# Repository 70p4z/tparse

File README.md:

# TParse

A minimalistic C library to parse text in microcontroller without memory allocation.

Supports:
- Hex arrays
- Hex integer
- Decimal integer
- List of allowed keywords
- Raw text token fetch

## IOBridge
A basic iobridge example project is provided, making extended use of the library.
The project is splitted in:
- A iobridge application for NUCLEO-L476RG;
- A python (3) library to communicate with.

The iobridge goal is to offer an UART driven text interface to bridge to various protocols (raw GPIO, I2C bus, CAN bus, ISO7816-3 T=0). The project will be extended with ADC, OneWire and SPI.

## Nucleo F767ZI solax pylontech
Sometimes it's harder than it looks to build a solar system with batteries from scratch. Especially if you build it from the electronic engineer point of view.
Voltage are in range, and the datasheets seems like a match. 
BUT it turns out you're missing the whole point. Many players in the ecosystem are not willing for compatibility. And the war moves from electronic to communication protocol to make systems work.

I got into such a refreshing problem when I decided to go solar with a huge amount of auto consumption. I went for modular Pylontech H48050 (high voltage (HV)) based system (SC0500 + 8 H48050 in the end). And tried to connect it with a Solax X1 Hybrid G4.

The very point is that it won't work until you ~handle~ rewrite some part of the protocol on the fly.

The example for nucleo was mainly done to have the communication working, and various tries to allow for power optimisation, or workaround on problems (not respected zero injection).

Anyway, this project is only based on tparse for the ring buffer management (but it started with 2 iobridges until I found a board (f767zi) that handle 2 CAN bus to perform the man-in-the-middle).

The project further grown into a fully fledged reporting system to connect with home assistant (through a http sensor python script running on a raspberry pi zero w).

I'll try to add a design later on to design the daughter board on the nucleo for the various connections (mate box relay, CAN to the inverter, CAN to the battery, I2C for the reporting, serial for the pocket wifi link).

Long story short, the bugfix for the protocol is to only patch the CAN message 0x1877 byte 4 from whatever (IIRC it was 0x01) to 0x83 to make the inverter happily use the BMS (and stop complaining about invalid voltage).

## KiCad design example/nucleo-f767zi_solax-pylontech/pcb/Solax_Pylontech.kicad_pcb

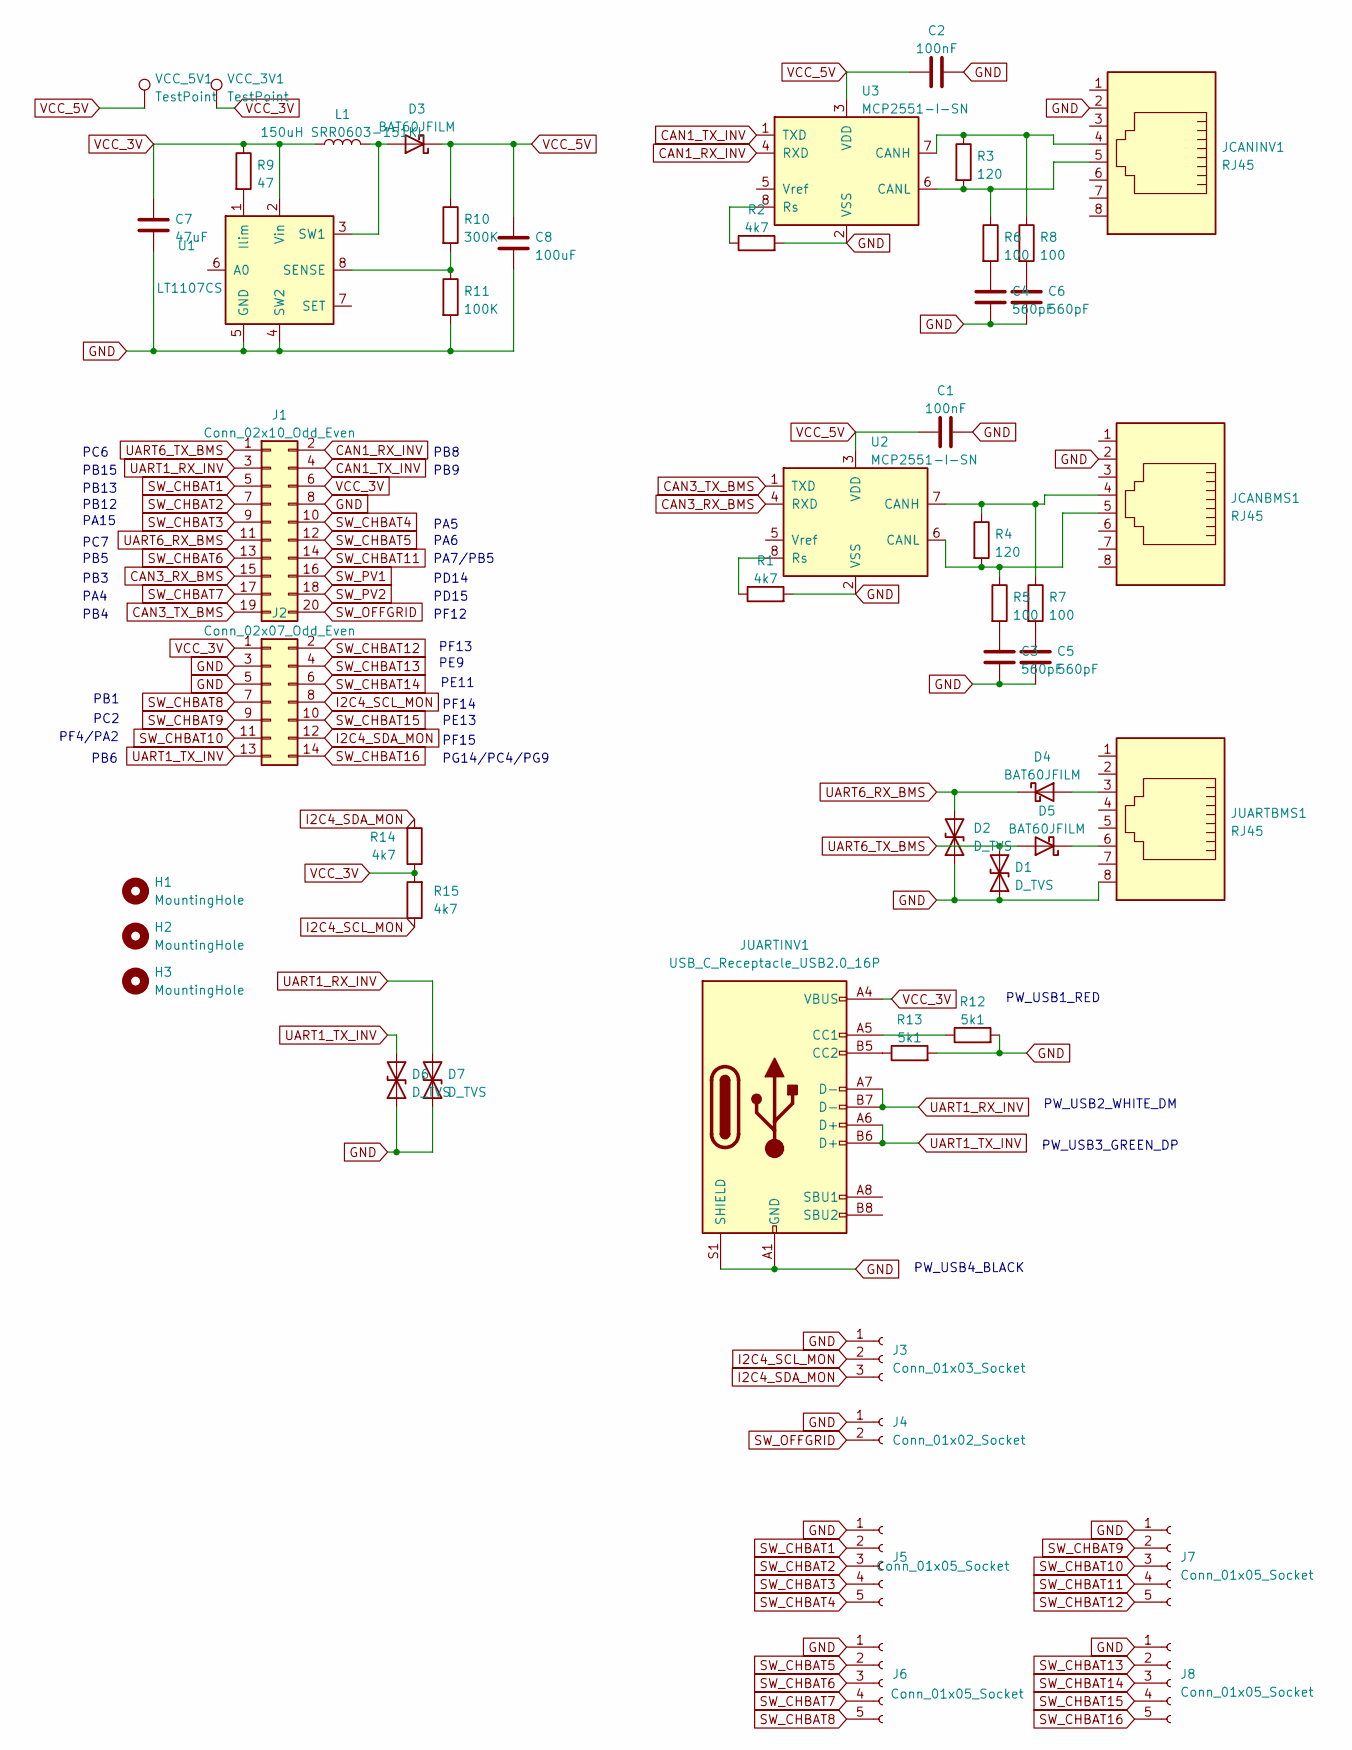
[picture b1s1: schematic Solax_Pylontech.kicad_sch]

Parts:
C1, C2: 100nF; C_0603_1608Metric
C3, C4, C5, C6: 560pF; C_0603_1608Metric
C7: 47uF; C_0805_2012Metric
C8: 100uF; C_0805_2012Metric
D1, D2, D6, D7: D_TVS; D_0603_1608Metric
D3, D4, D5: BAT60JFILM; D_SOD-323
H1, H2, H3: MountingHole; MountingHole_3mm
J1: Conn_02x10_Odd_Even; PinHeader_2x10_P2.54mm_Vertical
J2: Conn_02x07_Odd_Even; PinHeader_2x07_P2.54mm_Vertical
J3: Conn_01x03_Socket; JST_XH_B3B-XH-A_1x03_P2.50mm_Vertical
J4: Conn_01x02_Socket; JST_XH_B2B-XH-A_1x02_P2.50mm_Vertical
J5, J6, J7, J8: Conn_01x05_Socket; JST_XH_B5B-XH-A_1x05_P2.50mm_Vertical
JCANBMS1: RJ45; RJ45_Amphenol_54602-x08_Horizontal
JCANINV1: RJ45; RJ45_Amphenol_54602-x08_Horizontal
JUARTBMS1: RJ45; RJ45_Amphenol_54602-x08_Horizontal
JUARTINV1: USB_C_Receptacle_USB2.0_16P; USB_C_Receptacle_GCT_USB4105-xx-A_16P_TopMnt_Horizontal
L1: 150uH SRR0603-151KL; L_6.3x6.3_H3
R1, R2, R14, R15: 4k7; R_0603_1608Metric
R3, R4: 120; R_0603_1608Metric
R5, R6, R7, R8: 100; R_0603_1608Metric
R9: 47; R_0603_1608Metric
R10: 300K; R_0603_1608Metric
R11: 100K; R_0603_1608Metric
R12, R13: 5k1; R_0603_1608Metric
U1: LT1107CS; SOIC-8_3.9x4.9mm_P1.27mm
U2, U3: MCP2551-I-SN; SOIC-8_3.9x4.9mm_P1.27mm
VCC_3V1, VCC_5V1: TestPoint; TestPoint_THTPad_D2.0mm_Drill1.0mm

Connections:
CAN1_RX_INV: J1.2, U3.4 (RXD)
CAN1_TX_INV: J1.4, U3.1 (TXD)
CAN3_RX_BMS: J1.15, U2.4 (RXD)
CAN3_TX_BMS: J1.19, U2.1 (TXD)
GND: C1.2, C2.1, C3.2, C4.2, C5.2, C6.2, C7.2, C8.1, D1.1 (A1), D2.1 (A1), D6.1 (A1), D7.1 (A1), J1.8, J2.3, J2.5, J3.1, J4.1, J5.1, J6.1, J7.1, J8.1, JCANBMS1.2, JCANINV1.2, JUARTBMS1.8, JUARTINV1.A1 (GND), JUARTINV1.A12 (GND), JUARTINV1.B1 (GND), JUARTINV1.B12 (GND), JUARTINV1.S1 (SHIELD), R1.2, R2.2, R11.2, R12.2, R13.2, U1.4 (SW2), U1.5 (GND), U2.2 (VSS), U3.2 (VSS)
I2C4_SCL_MON: J2.8, J3.2, R15.1
I2C4_SDA_MON: J2.12, J3.3, R14.2
unnamed: C3.1, R5.2
unnamed: C4.1, R6.2
unnamed: C5.1, R7.2
unnamed: C6.1, R8.2
unnamed: D3.2 (A), L1.2, U1.3 (SW1)
unnamed: D4.2 (A), JUARTBMS1.3
unnamed: D5.1 (K), JUARTBMS1.6
unnamed: JUARTINV1.A5 (CC1), R12.1
unnamed: JUARTINV1.B5 (CC2), R13.1
unnamed: R9.2, U1.1 (Ilim)
unnamed: R10.2, R11.1, U1.8 (SENSE)
unnamed: JCANBMS1.4, R4.1, R7.1, U2.7 (CANH)
unnamed: JCANBMS1.5, R4.2, R5.1, U2.6 (CANL)
unnamed: R1.1, U2.8 (Rs)
unnamed: JCANINV1.4, R3.1, R8.1, U3.7 (CANH)
unnamed: JCANINV1.5, R3.2, R6.1, U3.6 (CANL)
unnamed: R2.1, U3.8 (Rs)
SW_CHBAT1: J1.5, J5.2
SW_CHBAT2: J1.7, J5.3
SW_CHBAT3: J1.9, J5.4
SW_CHBAT4: J1.10, J5.5
SW_CHBAT5: J1.12, J6.2
SW_CHBAT6: J1.13, J6.3
SW_CHBAT7: J1.17, J6.4
SW_CHBAT8: J2.7, J6.5
SW_CHBAT9: J2.9, J7.2
SW_CHBAT10: J2.11, J7.3
SW_CHBAT11: J1.14, J7.4
SW_CHBAT12: J2.2, J7.5
SW_CHBAT13: J2.4, J8.2
SW_CHBAT14: J2.6, J8.3
SW_CHBAT15: J2.10, J8.4
SW_CHBAT16: J2.14, J8.5
SW_OFFGRID: J1.20, J4.2
SW_PV1: J1.16
SW_PV2: J1.18
UART1_RX_INV: D7.2 (A2), J1.3, JUARTINV1.A7 (D-), JUARTINV1.B7 (D-)
UART1_TX_INV: D6.2 (A2), J2.13, JUARTINV1.A6 (D+), JUARTINV1.B6 (D+)
UART6_RX_BMS: D2.2 (A2), D4.1 (K), J1.11
UART6_TX_BMS: D1.2 (A2), D5.2 (A), J1.1
VCC_3V: C7.1, J1.6, J2.1, JUARTINV1.A4 (VBUS), JUARTINV1.A9 (VBUS), JUARTINV1.B4 (VBUS), JUARTINV1.B9 (VBUS), L1.1, R9.1, R14.1, R15.2, U1.2 (Vin), VCC_3V1.1
VCC_5V: C1.1, C2.2, C8.2, D3.1 (K), R10.1, U2.3 (VDD), U3.3 (VDD), VCC_5V1.1

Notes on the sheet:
PA4
PD14
PA6
PC6
PB13
PB3
PB15
PW_USB3_GREEN_DP
PE9
PA7/PB5
PD15
PC2
PB9
PB8
PB5
PB4
PW_USB2_WHITE_DM
PC7
PE11
PF14
PG14/PC4/PG9
PE13
PW_USB1_RED
PA15
PW_USB4_BLACK
PF13
PB12
PB1
PF4/PA2
PF15
PF12
PA5
PB6

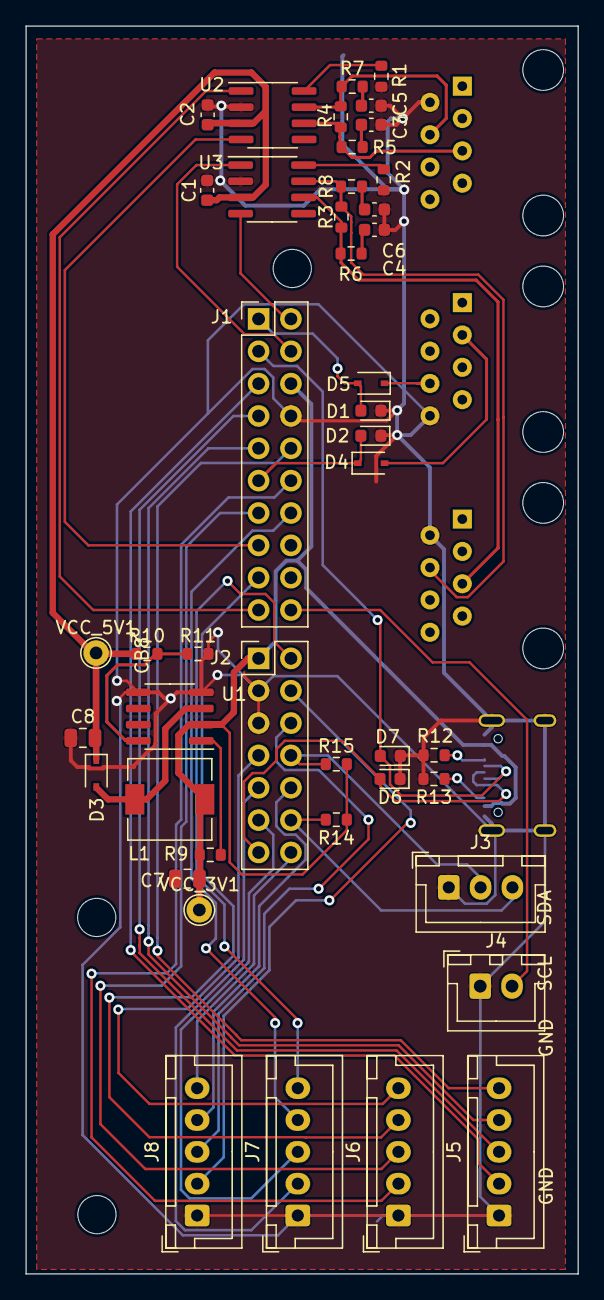
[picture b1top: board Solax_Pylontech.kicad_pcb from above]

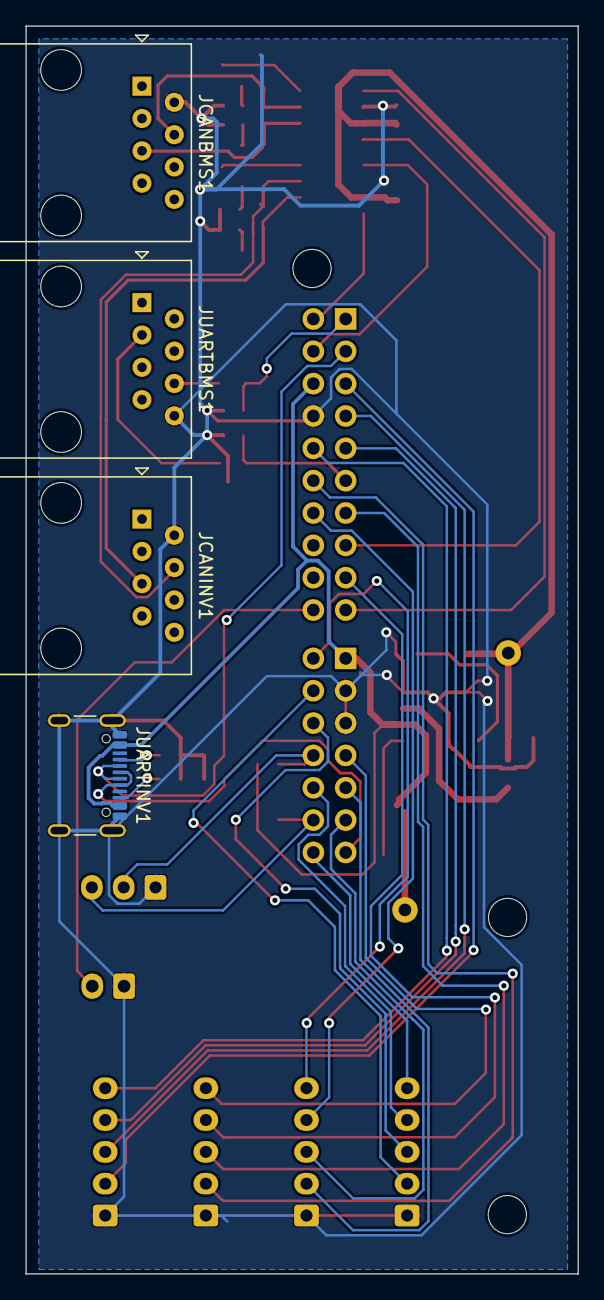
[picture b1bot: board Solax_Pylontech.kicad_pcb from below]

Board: 2 copper layers, 43.4 x 98.0 mm, 51 parts (4 on the bottom side), 47 nets.

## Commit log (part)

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2022-05-04 initial import
2022-05-05 stm32l476 iobridge
2022-05-07 add token_count for the unconsommed line + tests, add eol_reached check
2022-05-07 iobridge exti in polling (sometimes, it was not detected 8|), move timeout definition
2022-05-16 fix token_size to correctly return when token is at end of buffer, and delimiter is on the first buffer entry (i.e. "\n...token")
2022-05-17 remove debug stuff for previous token at end of buffer bug
2022-05-17 iobridge python for can bus with fixed mitm example
2022-05-22 fix out of bound receiving can frames
2022-05-22 fix i2c_cargo transport python script
2022-05-23 discard problematic tx requests
2022-05-30 - add i2c retry count to command in case of NAKed addresses - refactor iobridge uart sync
2022-06-07 - update usart<->pc bitrate - add isocfg and i2cfg commands - support ATR TA1 force to try negociating over the proposed max of a smartcard - fixup gpi command in case of unconfgured pin (must not be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
2022-06-08 update bitrate of the iobridge in its various base tools
2022-06-18 fixup swapped comments
2022-06-20 solax bms: add timeout during cavail requests, and add bms ping to startup the BMS without grid (to power up the off grid mode
2022-06-20 fix invalid i2c address check
2022-07-19 allow to set the i2c int pin with cargo operations
2022-08-30 fixup io troubles during transport of cached T0 APDU => python timeout in case of hard timeout
2022-10-16 store the first description of the BMS at boot
2022-10-31 change output files to avoid stm32cubeprogrammer to complain (not finding files)
2022-11-03 i2c: add clock (bitrate) configuration
2022-11-15 bump bridge's version and make use of i2c cached transfers to optimize the whole applications
2022-12-01 resynch slave board at startup for Pylontech/Solax correct communication
2022-12-16 add tparse_discard implementation
2022-12-17 fix chec to avoid disurbing battery SoC at night
2022-12-27 fix solax patch optimization for dawn/dusk and low solar
2022-12-27 solax: split invalidity checks to enhance user display
2022-12-27 solax bridge: commit output file for the solax master
2022-12-29 enhance battery display (try to correct the inverter battery invalid value)
2022-12-31 - more code annotation - reverse sign of export constan for easier computation understanding - add condition when engaging selfuse and not reached the 80% SoC, to ensure the battery continues to char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
2023-01-03 - reduce work mode change delay - fix invalid can standard marker - fix typo
2023-01-08 fixup CAN timings to avoid pylontech desynch
2023-01-08 only override max charge when not 100% SoC
2023-01-08 - fix battery wattage display (in both charge and discharge) - avoid wattage min value for self use switch rule when soc above threshold - set charge to 0A when overriding the mode (to forced stop)
2023-01-08 add cause display index for selfuse return rule
2023-01-10 put solax/pylontech var globals, and wipe them
2023-01-10 reencode errors, avoid dispaing with errors
2023-01-10 add i2c data output for home automation
2023-01-14 - add prints on the master uart for debug purpose - fixup rule 7 to avoid reporting battery charge max - fixup rule 5 requirement (grid_wattage must be over the optimization threshold (to debounce sm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
2023-01-16 force battery to 100% from the inverter point of view in optimization cases
2023-01-27 - refactor naming, output more data toward home assistant
2023-01-27 add a watchdog and a software io stall timeout to reset the bridge whenever a bad condition is detected
2023-03-21 try to fix a spurious overflow
2023-03-21 add fields (eps and pv state)
2023-03-23 fix definition of buffer size, also support pocketwifi regular settings read that kills the values (with a race condition on buffer access)
2023-04-04 add the previous version
2023-04-16 - add support for BMS RS232 precise current reading - rework pinout to minimize daughter board on nucleo - add daughter board design and gerbers for nucleo-f767zi - change type for 8 H48050 packs con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
2023-04-17 tparse: add test to parse negative integers example/nucleo/solax: add rendered schematic as pdf
2023-04-25 iobridge update to support mtu negociation and factorize all instructions for I2C cargo transport
2023-05-09 fix invlid inner loop exit during cargo i2c transfer
2023-05-14 fixup rs232 current direction on the pylontech SC0500-40s BMS
2023-06-06 silly previous patch reworked
2023-06-14 - bump version - add pylontech CAN cache to avoid power loss upon temporary CAN bus glitch - fix CAN bus 500kbit/s timing on STM32 bxCAN - add 98% SoC battery drain before PV powering bug in the Sola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
2023-06-23 add stm32l0xx (tested on STM32L053) port of iobridge (without CAN)
2023-07-18 mqtt: cleanup upon disconnect/exit
2023-09-08 reduce logging verbosity
2023-09-08 avoid battdrain fix > 97% when battery is not drained, else it creates charging spikes
2023-11-12 - fix cause 78 when gridtie and not selfusing (idle) - add control over selfuse anto mode and grid connection severance through DIN relay - remove unused and wrong code for battery full hicups - add 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
2023-11-13 clock on hsi for stm32l0xx
2023-11-18 correctly publish inverter state on mqtt for home assistant to display it
2023-11-26 - cleanup, remove dead/unused code, fix too much message for gridtie/offline decision - force taking into account consumption of inverter in max charge limit
2023-12-12 remove unused define
2023-12-12 don't update global vars with maxcharge/dischagre values until we know we're not in the 2^31 bug
2023-12-12 fix too much EPS switches and fix condition to perform switches
2023-12-14 decode additional data from the pylontech frame
2023-12-14 make disjoint selfuse auto and eps switch auto, as it could lead to unwanted injection
2023-12-14 consider a longer CAN timeout for a reset decision, to avoid outtages)
2023-12-14 commit the binaries
2024-01-15 - add i32 parsing + test - fix precise wattage computation (avoid int32_t overflow)
2024-01-17 add example of the USART BMS OUTPUT
2024-01-21 support skipping multiple concatenated delimiters (aside from \n) between tokens
2024-01-21 - parse precise capacity from the usart bms output, and report it through mqtt - implement precise wattage when BMS does not report current flow
2024-02-01 add SPI support to the list of talked protocols (mainly for MAX7219 interfacing)
2024-02-02 port SPI interfacing onto the L0
2024-02-13 fix battery mAh report
2024-03-05 - add release instruction to put all IOs into highZ, requires issuing reset instruction before any further digital communication again (JTAG and USART to PC IOs are not set highZ) - add missing intf 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
2024-03-28 add config pin as input to enable high Z state
2024-03-31 avoid normal window before severing grid link due to status stabilisation
2024-05-15 fix cargo to negociate MTU
2024-05-15 forced batt charge SoC set to 75% instead of 90% to ensure always respected (it's unlikely the inverter charge SoC is below 75)
2024-05-15 add a slow charge without timeout add a timeout to forced charge to avoid forgetting it set slow forced charge to 0.3A to force the SolAX X1G4 to avoid draining batteries without exploiting PV max av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
2024-05-16 fix batt_forced_max charge invalid overidden value, remove unused ref to forcing
2024-05-16 avoid stop timer for forced charge, use the voltage limit instead in the fw
2024-05-23 limit wear (especially when small balancing is required)
2024-05-23 commit binaries
2024-06-14 update "anti battery drain first when battery is full" workaround, using a sliding average of the battery link, and compensate it
2024-11-21 change boundaries of the charge/discharge to 20%/100%, this is LFP!
2024-11-21 more logs to detect feilure (which was due to invalid usb connector in the inverter :()
2024-11-21 add i2c strobe to detect i2c devices
2024-11-28 - FIX stall in I2C interrupt, leading to reset and gridtie force messing around (possibly disrupting expected behavior of the house main contactor) - rmeove unused constant (uart wait) - i2c clear er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
2024-11-28 - fix invalid forced current accuracy value to 0.1A - commit generated binaries
2024-12-15 fix log message
2024-12-15 remove unused match for 1871 from BMS
2024-12-15 update binary for nucleo board
2024-12-26 aviid overcharge when overvoltage detected.
2025-01-23 ensure 100% charge when charge is effectively finished (overvoltage detected)
2025-01-31 - support forced SoC to allow for PV -> grid and PV -> batt, but no batt -> grid (selfuse, without battery drain)
2025-02-16 - fix battery pack parse for min/max voltage - fix battery pack reporting order on I2C to go from closest to farthest
2025-03-01 rework mqtt interface for forced max current (negative value disable it, as per SoC override)
2025-03-03 safety: add a grid force disconnect to circumvent the batteryfull + force continue charging of the inverter
2025-03-04 fixup invalid direction check to grab the highest cell's voltage
2025-03-30 adjust the relay handling when starting in EPS mode
2025-05-16 fix handling of invalid voltage in balancing algorithm
2025-05-23 iobridge server mode, to allow for multiple application using the same board to use a isngle uart connection
2025-06-03 update the max wattage to allow for correct compensation
2025-08-13 update auto current algorithm to be more reactive using delta instead of +1/-1 increase refactor to extract the battery full drain workaround and make it testable change the grid disconnect SoC to 80%
2025-08-13 set battery SoC to grid connect - 1, to ensure Solax to perform PV->GRID, and remaining PV->BATT, instead of having PV+BATT->GRID, very useful when low sun exposure per day (to limit number of grid c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
2025-12-03 rework notification of forced states
2025-12-03 update binaries
2025-12-04 avoid bug leading to invalid apparent soc always applied even when battery goes real low
2025-12-04 remove useless recheck
2025-12-05 add hysterisis management for the enable-self-use / disable-self-use to avoid battery discharge on that period
2026-02-18 - implement battery balancing using external charger in front of each pack (HDR-15-48), each one driven by a triac module (MRA-23D2) - add home assistant shenanigans to drive the battery balancing (m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
2026-02-19 - implement safety to stop balancing - continue charging the selected pack until a minimum gap is reached before either charging another pack OR stop balancing
2026-02-26 fix forced max battery charge wattage (not compensated for internal solax current draw
2026-03-02 add limited charge over a given max cell voltage (to allow for balancing to operate cleanly, without the "rush to 3.6V" of the pylontech BMS
2026-03-03 add few cases for offgrid switch activation
2026-03-03 when a knobs value is used to force charge voltage, discard auto balancing end of charge to avoid perturbation
2026-03-03 increase delay between averagging of currnt to avoid infernal loop of retroaction with delay on the battery charge link when value applied
2026-03-03 use more precise vcell for checks
2026-03-05 fix too huge current swings
2026-03-10 auto chare current refactor, to add a smoothing on end of charge without hiccups
2026-03-23 fixup limit to start managed charging
2026-04-06 - compile using optimized version - add makefile target for nucleo on sdb, when sda is already plugged in :)
2026-04-10 fixup hysterisis end of charge
2026-04-13 PID commented code cleanup
2026-04-13 - better handle BMS cell values to avoid possibly long period without updated values
2026-04-17 - fix maxch negative value (invalid, always interpreted as UINT16 in the CAN protocol - fix limited charge current target, that was too low previously - add test for end of charge - fix bms_charge_pi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
